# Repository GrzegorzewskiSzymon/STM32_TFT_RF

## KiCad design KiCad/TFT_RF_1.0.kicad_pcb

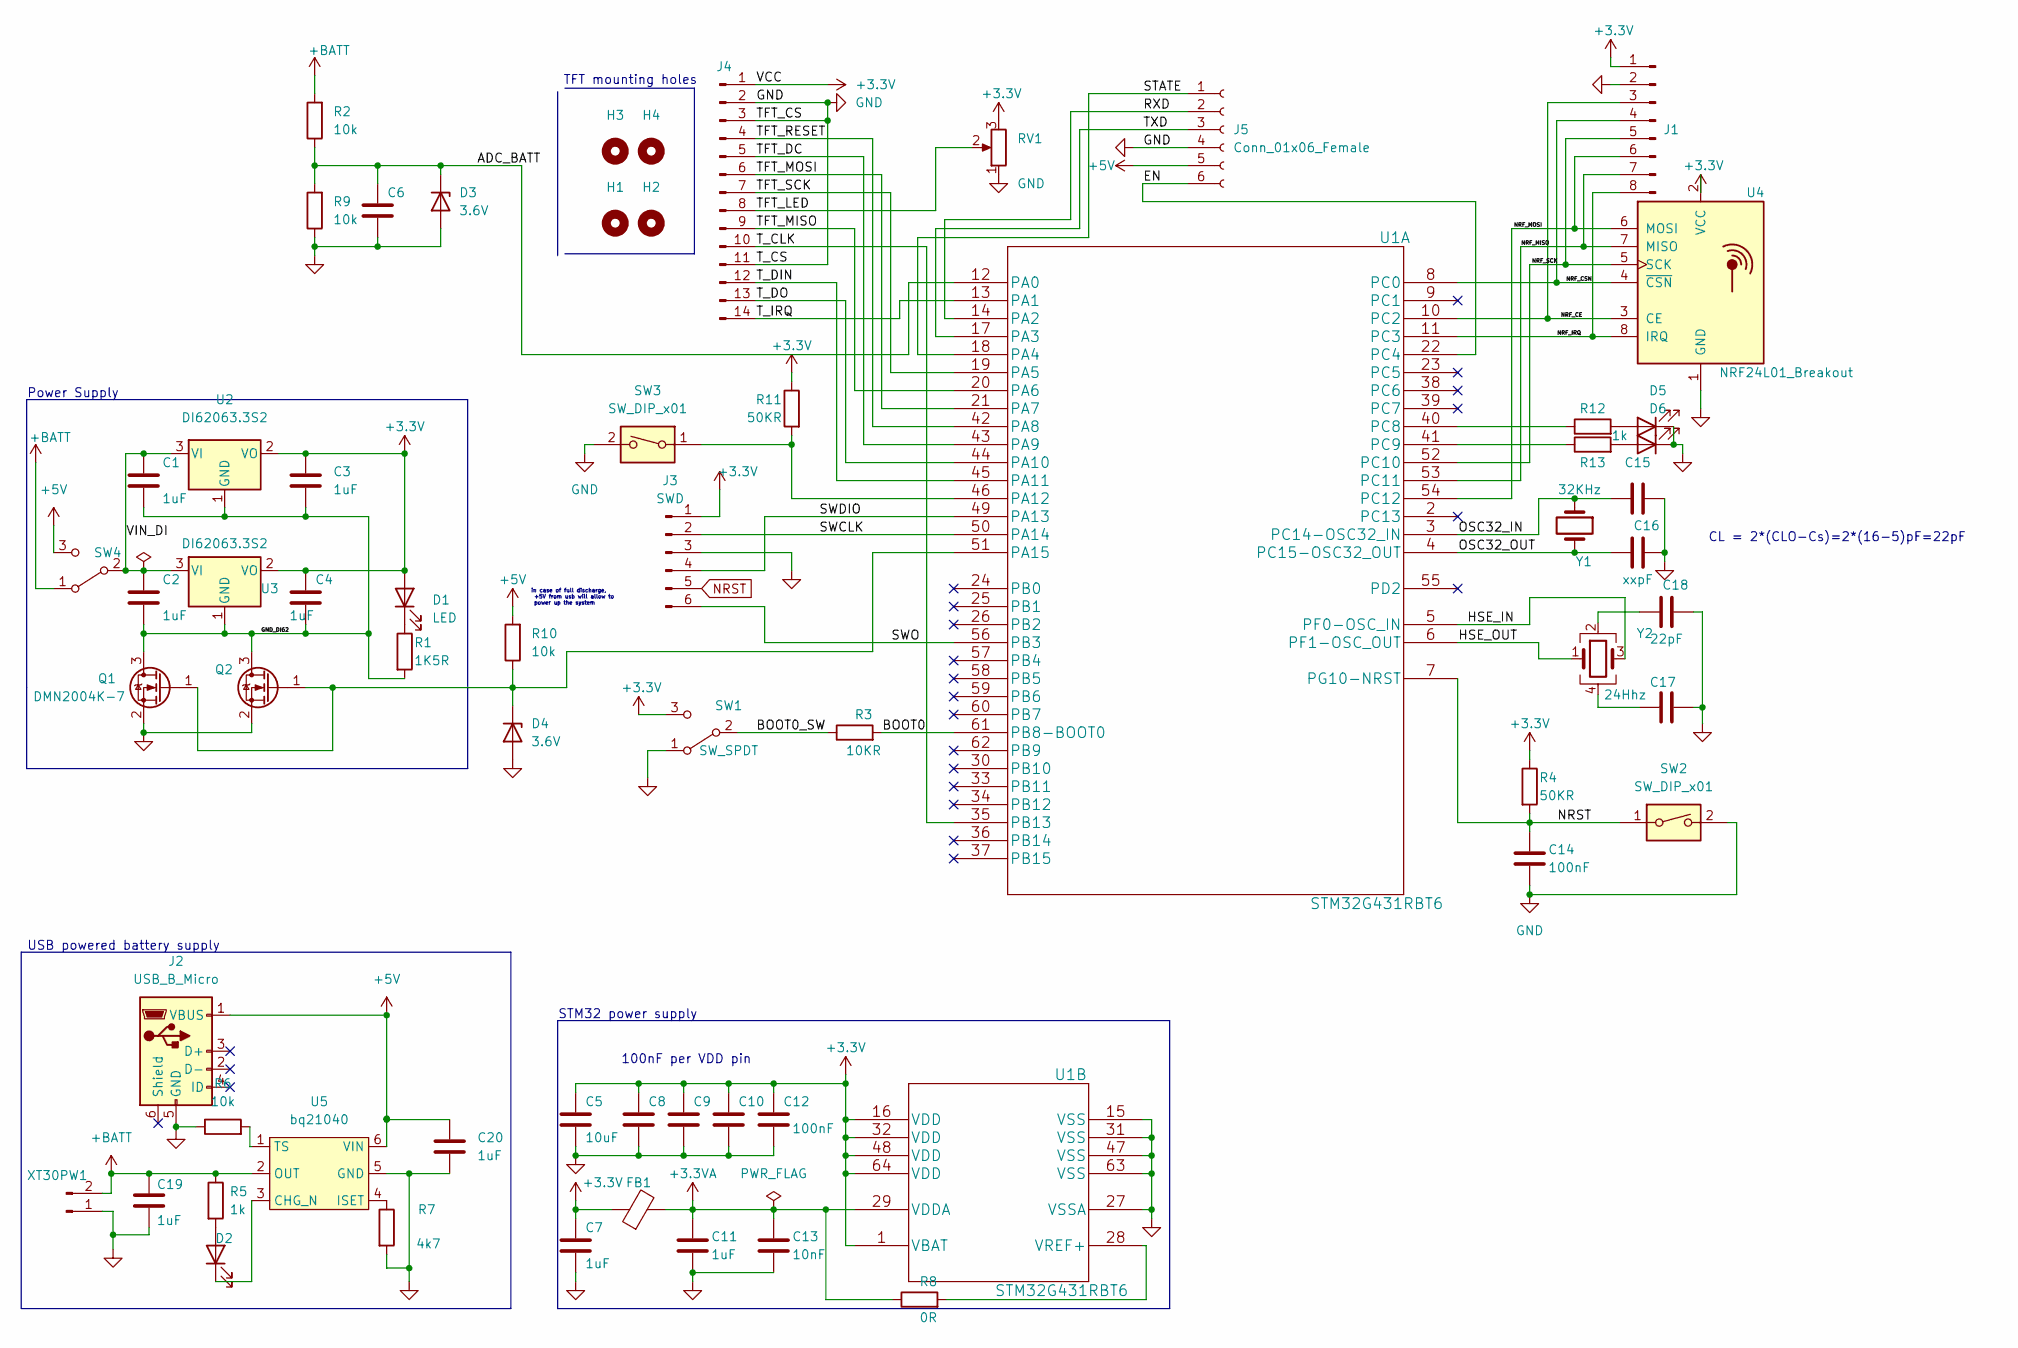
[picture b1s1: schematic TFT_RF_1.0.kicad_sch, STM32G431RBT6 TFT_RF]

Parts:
C1, C2, C3, C4, C7, C11, C19, C20: 1uF; L_0805_2012Metric_Pad1.15x1.40mm_HandSolder
C5: 10uF; L_0805_2012Metric_Pad1.15x1.40mm_HandSolder
C6, C8, C9, C10, C12, C14: 100nF; L_0805_2012Metric_Pad1.15x1.40mm_HandSolder
C13: 10nF; L_0805_2012Metric_Pad1.15x1.40mm_HandSolder
C15, C16: xxpF; L_0805_2012Metric_Pad1.15x1.40mm_HandSolder
C17, C18: 22pF; L_0805_2012Metric_Pad1.15x1.40mm_HandSolder
D1, D2, D5, D6: LED; R_0805_2012Metric_Pad1.20x1.40mm_HandSolder
D3, D4: 3.6V; Nexperia_CFP3_SOD-123W
FB1: 120R 100MHz; BDS
H1, H2, H3, H4: MountingHole; MountingHole_3.2mm_M3
J1: Conn_01x08_Male; PinHeader_1x08_P1.27mm_Vertical
J2: USB_B_Micro; USB_Micro-B_Molex_47346-0001
J3: SWD; PinHeader_1x06_P2.54mm_Vertical
J4: Conn_01x14_Male; PinHeader_1x14_P2.54mm_Vertical
J5: Conn_01x06_Female; PinSocket_1x06_P2.54mm_Vertical
Q1, Q2: DMN2004K-7; SOT-23
R1: 1K5R; R_1206_3216Metric_Pad1.30x1.75mm_HandSolder
R2, R6, R9, R10: 10k; R_1206_3216Metric_Pad1.30x1.75mm_HandSolder
R3: 10KR; R_1206_3216Metric_Pad1.30x1.75mm_HandSolder
R4, R11: 50KR; R_1206_3216Metric_Pad1.30x1.75mm_HandSolder
R5, R12, R13: 1k; R_1206_3216Metric_Pad1.30x1.75mm_HandSolder
R7: 4k7; R_1206_3216Metric_Pad1.30x1.75mm_HandSolder
R8: 0R; R_1206_3216Metric_Pad1.30x1.75mm_HandSolder
RV1: R_Potentiometer; Potentiometer_ACP_CA9-H5_Horizontal
SW1, SW4: SW_SPDT; os102011
SW2, SW3: SW_DIP_x01; SW_PUSH_6mm_H4.3mm
U1: STM32G431RBT6; LQFP-64_10x10mm_P0.5mm
U2, U3: DI62063.3S2; SOT-23
U4: NRF24L01_Breakout; nRF24L01_Breakout
U5: bq21040; TSOT-23-6_HandSoldering
XT30PW1: Conn_01x02_Male; AMASS_XT30PW-M_1x02_P2.50mm_Horizontal
Y1: 32KHz; Crystal_DS10_D1.0mm_L4.3mm_Horizontal_1EP_style2
Y2: 24Hhz; Crystal_SMD_SeikoEpson_FA238-4Pin_3.2x2.5mm_HandSoldering

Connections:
+3.3V: C3.1, C4.1, C5.1, C7.1, C8.1, C9.1, C10.1, C12.1, D1.2 (A), FB1.1, J1.1, J3.1, J4.1, R4.1, R11.1, RV1.3, SW1.3 (C), U1.1 (VBAT), U1.16 (VDD), U1.32 (VDD), U1.48 (VDD), U1.64 (VDD), U2.2 (VO), U3.2 (VO), U4.2 (VCC)
+3.3VA: C11.1, C13.1, FB1.2, R8.1, U1.29 (VDDA)
+5V: C20.1, J2.1 (VBUS), J5.5, R10.2, SW4.3 (C), U5.6 (VIN)
+BATT: C19.1, R2.2, R5.1, SW4.1 (A), U5.2 (OUT), XT30PW1.2
/ADC_BATT: C6.1, D3.1 (K), R2.1, R9.2, U1.12 (PA0)
/BOOT0: R3.2, U1.61 (PB8-BOOT0)
/BOOT0_SW: R3.1, SW1.2 (B)
/EN: J5.6, U1.22 (PC4)
/GND_DI62: C1.2, C2.2, C3.2, C4.2, Q1.3 (D), Q2.3 (D), R1.2, U2.1 (GND), U3.1 (GND)
/HSE_IN: U1.5 (PF0-OSC_IN), Y2.3
/HSE_OUT: U1.6 (PF1-OSC_OUT), Y2.1
/NRF_CE: J1.3, U1.10 (PC2), U4.3 (CE)
/NRF_CSN: J1.4, U1.8 (PC0), U4.4 (~CSN)
/NRF_IRQ: J1.8, U1.11 (PC3), U4.8 (IRQ)
/NRF_MISO: J1.7, U1.53 (PC11), U4.7 (MISO)
/NRF_MOSI: J1.6, U1.54 (PC12), U4.6 (MOSI)
/NRF_SCK: J1.5, U1.52 (PC10), U4.5 (SCK)
/OSC32_IN: C15.1, U1.3 (PC14-OSC32_IN), Y1.1
/OSC32_OUT: C16.1, U1.4 (PC15-OSC32_OUT), Y1.2
/RXD: J5.2, U1.14 (PA2)
/STATE: J5.1, U1.18 (PA4)
/SWCLK: J3.2, U1.50 (PA14)
/SWDIO: J3.4, U1.49 (PA13)
/SWO: J3.6, U1.56 (PB3)
/TFT_DC: J4.5, U1.43 (PA9)
/TFT_LED: J4.8, RV1.2
/TFT_MISO: J4.9, U1.20 (PA6)
/TFT_MOSI: J4.6, U1.21 (PA7)
/TFT_RESET: J4.4, U1.42 (PA8)
/TFT_SCK: J4.7, U1.19 (PA5)
/TXD: J5.3, U1.17 (PA3)
/T_CLK: J4.10, U1.35 (PB13)
/T_DIN: J4.12, U1.45 (PA11)
/T_DO: J4.13, U1.44 (PA10)
/T_IRQ: J4.14, U1.13 (PA1)
/VIN_DI: C1.1, C2.1, SW4.2 (B), U2.3 (VI), U3.3 (VI)
GND: C5.2, C6.2, C7.2, C8.2, C9.2, C10.2, C11.2, C12.2, C13.2, C14.2, C15.2, C16.2, C17.1, C18.2, C19.2, C20.2, D3.2 (A), D4.2 (A), D5.1 (K), D6.1 (K), J1.2, J2.5 (GND), J3.3, J4.2, J4.3, J4.11, J5.4, Q1.2 (S), Q2.2 (S), R6.1, R7.2, R9.1, RV1.1, SW1.1 (A), SW2.2, SW3.2, U1.15 (VSS), U1.27 (VSSA), U1.31 (VSS), U1.47 (VSS), U1.63 (VSS), U4.1 (GND), U5.5 (GND), XT30PW1.1
NRST: C14.1, J3.5, R4.2, SW2.1, U1.7 (PG10-NRST)
unnamed: C17.2, Y2.4
unnamed: C18.1, Y2.2
unnamed: D1.1 (K), R1.1
unnamed: D2.1 (K), U5.3 (CHG_N)
unnamed: D2.2 (A), R5.2
unnamed: D5.2 (A), R12.2
unnamed: D6.2 (A), R13.2
unnamed: D4.1 (K), Q1.1 (G), Q2.1 (G), R10.1, U1.51 (PA15)
unnamed: R6.2, U5.1 (TS)
unnamed: R7.1, U5.4 (ISET)
unnamed: R8.2, U1.28 (VREF+)
unnamed: R12.1, U1.40 (PC8)
unnamed: R13.1, U1.41 (PC9)
unnamed: R11.2, SW3.1, U1.46 (PA12)

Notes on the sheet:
STM32 power supply
USB powered battery supply
100nF per VDD pin
TFT mounting holes
in case of full discharge, +5V from usb will allow to power up the system
CL = 2*(CLO-Cs)=2*(16-5)pF=22pF
Power Supply

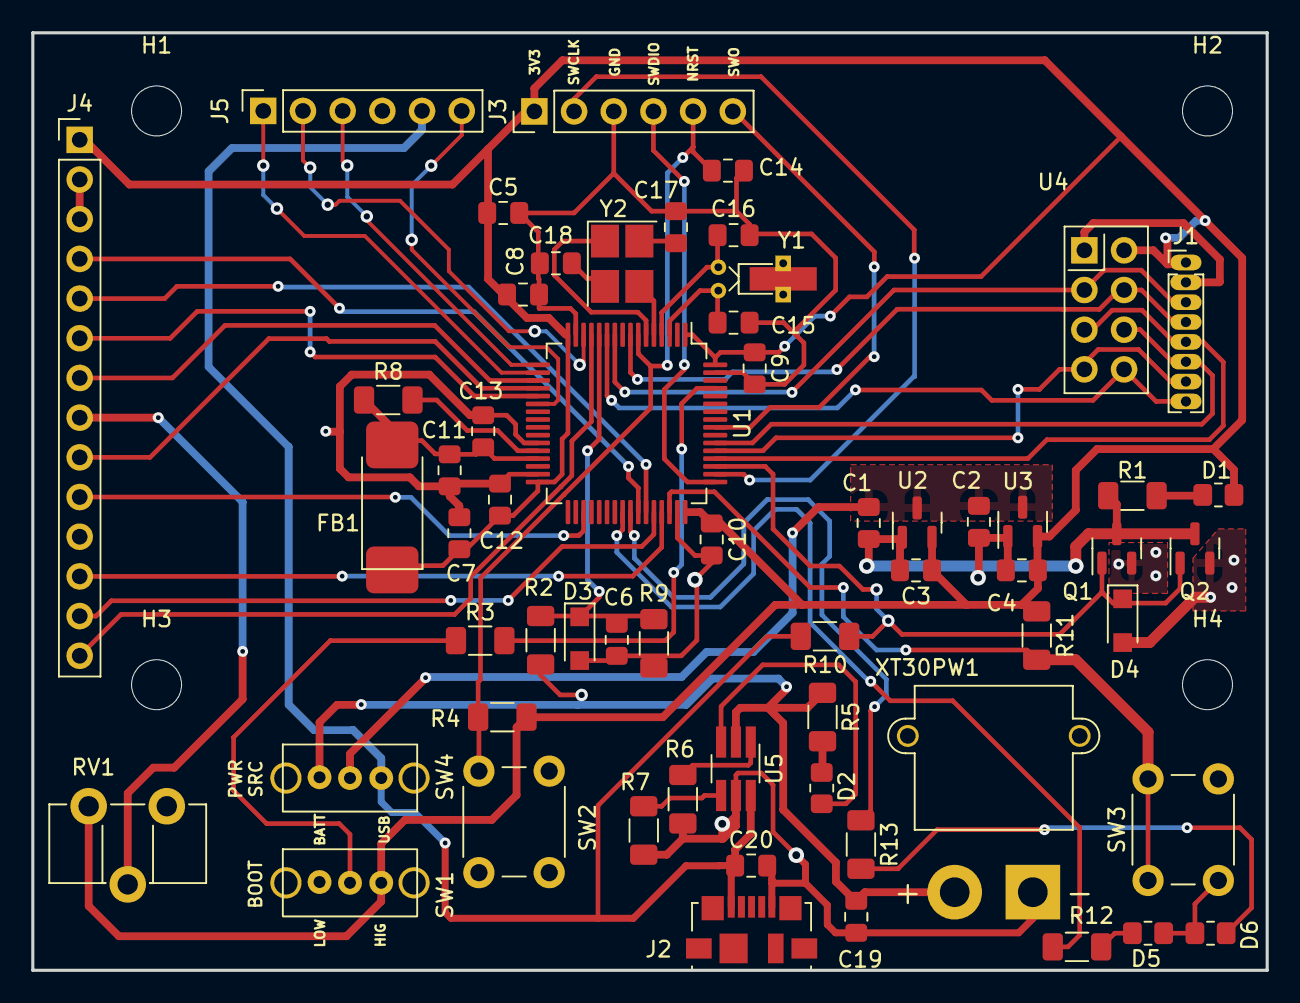
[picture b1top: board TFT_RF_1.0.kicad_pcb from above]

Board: 2 copper layers, 79.0 x 60.0 mm, 64 parts (0 on the bottom side), 52 nets.

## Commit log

2022-12-29 add: define ILI9341 registers addresses
2023-01-02 add basic functions to control ILI9341 with initialization
2023-01-02 add function to draw pixels on TFT
2023-01-03 fix ILI9341_DrawPixel function
2023-01-03 extract ILI9341_setFrame() from ILI9341_DrawPixel()
2023-01-03 fix overflow in ILI9341_DrawPixel
2023-01-03 add function ILI9341_DrawImg to draw previously generated pictures
    add picture to flash
2023-01-03 add function ILI9341_seRotation to rotate TFT
2023-01-04 add functions to activate and deactivate idle mode of ILI9341
2023-01-04 improve code clarity
2023-01-11 move everything related to registers to /RegistersConfig/ folder improve code clarity
2023-01-12 add configuration of SPI2, to communicate with XPT2046
2023-01-12 move spi_ili9341 functions to /TFT_ILI9341/ folder
2023-01-13 attach pins to spi2 (xtp2046)
    configure interrupt form PB3 (on line EXTI3) and add handler
2023-01-14 add XPT2046 setup function
2023-01-14 SPI2 - add function to simontainously receive and transmit data
    add function to read raw data from xpt2046
2023-01-15 add function to calculate touched pixel from raw data
2023-01-15 add full handling of detecting a touch and then take samples
2023-01-16 add .gitignore
2023-01-16 add /RegistersConfig/ with sysclk 170MHz initialization and GPIOA setup
2023-01-16 add spi3 functions for future communication with nrf24l01
2023-01-16 add NRF24L01 files and attach SPI3
2023-01-16 attach pins to spi3
2023-01-16 configure all needed pins for NRF24L01
2023-01-17 add basic functions to communicate with NRF24L01
2023-01-17 add NRF24L01 memory map
2023-01-19 add NRF24L01 basic initialization with transmitting part
2023-01-27 add receiving and transmitting part of initialization
2023-02-10 change pinout on spi 3 (RegistersConfig.*)
    fix receiving functions (RegistersConfig.c)
    change initialization from transmitting to receiving (main.c)
2023-02-17 remove unnecessary code update .gitignore (after renaming project)
2023-02-17 add initializations of pins for battery management create BatteryManagement files
2023-02-18 replace not stable functions for receiving (spi3) and implement them into NRF24L01
    previously NRF24L01_Receive() received halfway wrong data
    and NRF24L01_ReadReg(uint8_t reg) was overengineered due to bugs in receiving
2023-02-24 add ADC1 initialization and single channel conversion
    to monitor the battery voltage
2023-02-27 add TIM3 to activate ADC conversion cyclically
    conversion have interval of 1s, then after receiving
    interrupt from ADC, we handle it and transfer data to
    uint16_t battRawVoltageData
2023-03-02 add internal calibration of ADC1
2023-03-03 add CalculateBattVolatage() function
    and improve code clarity
    all battery related data is stored in (struct battery)
2023-03-03 clone and clear
2023-03-03 move files
2023-03-04 add register layer for SPI1 (connected to ILI9341)
2023-03-04 add files for gui
2023-03-04 change from predefined rotation of LCD to variable
2023-03-05 add few drawing functions
2023-03-05 add displaying buttons in DesktopLayer
2023-03-05 add settings button
2023-03-05 add function to display button
2023-03-06 add writing functions on LCD
2023-03-06 add possibility to set background color when writing on TFT
2023-03-09 add: display voltage and battery percentage every second
2023-03-09 add image to every button
2023-03-09 fix battery percentage calculation
2023-03-10 Clone touch functions
2023-03-10 initialize TouchScreen, attach pins to spi2 and EXTI1
2023-03-10 add state machine to displaying layers
2023-03-10 add simple setting layer
2023-03-11 add a state machine to identify if any button is touched
2023-03-11 Exclude possibility of occurring interrupt witch another drawing function while drawing a layer
2023-03-11 Add layer to control RGB leds
2023-03-11 fix displaying rounded rectangle
2023-03-21 -add: prevent multiple read of one touch -add: button to change rotation of TFT -fix: reading touched point in horizontal rotation
2023-03-21 add: prevent from draining battery below 3.7V
2023-05-29 fix bit operations controlling MOSFETS
2023-05-29 Add buffer of battery voltage samples to improve stability of calculations
2023-06-03 Add schematics and pcb layout with extracted gerber files
2023-06-04 add separate function to send whole data
2023-06-04 add simple sliders to adjust RGB colors
2023-06-04 add: send RGB data to another receiver
